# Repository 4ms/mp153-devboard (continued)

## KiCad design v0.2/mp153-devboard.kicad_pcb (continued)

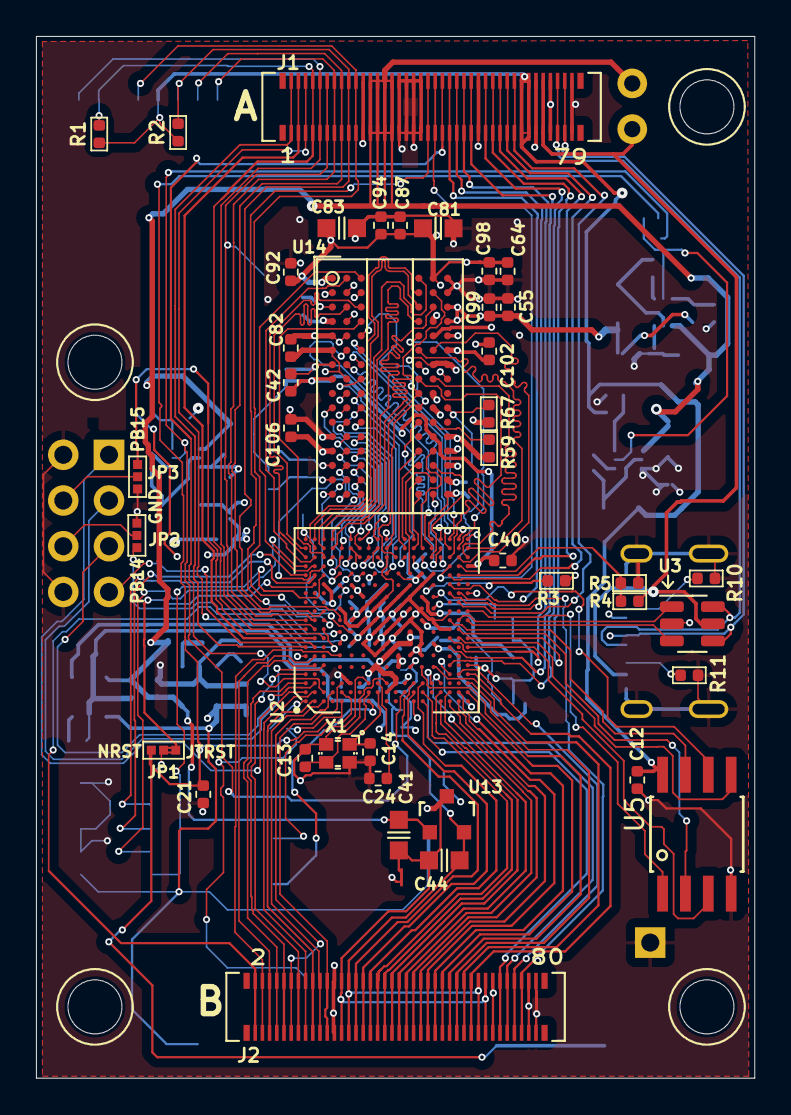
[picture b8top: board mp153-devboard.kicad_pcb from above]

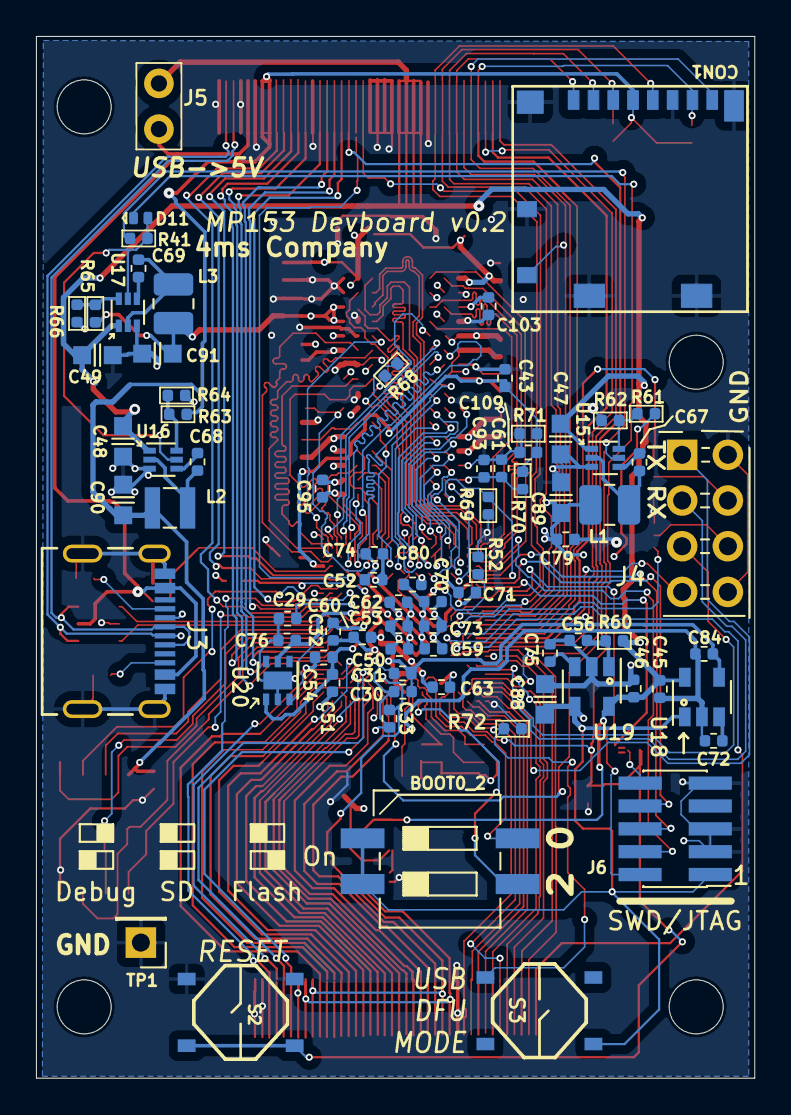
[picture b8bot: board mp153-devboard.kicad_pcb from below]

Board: 4 copper layers, 39.9 x 57.9 mm, 122 parts (76 on the bottom side), 168 nets.

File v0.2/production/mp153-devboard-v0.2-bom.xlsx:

mp153-devboard-v0.2-bom
4ms Company
PCBA Project: | mp153-devboard | Revision: | v0.2
EMAIL: | 4ms@4mscompany.com
DATE: | 2025-07-10
Group | Item# | Manufacturer | Manufacter Part# | Designator | Quantity | Designation | Package | Comments | Supplied by:
A | 1 | Hirose | DF40C-80DP-0.4V(51) | J1, J2 | 2 | Pins_02x40_P0.4mm_W3.0mm_SMT | Connector-80pin-P0.4mm-W3.0mm
A | 2 | Molex | 217179-0001 | J3 | 1 | USB-C_Receptacle_Molex_2171790001 | USB_C_Receptacle_Molex_2171790001
A | 3 | CTS | 219-2MST | BOOT0_2 | 1 | SW_DIP_x02_CTS_219-2MST, DIP Switch SPST x 2, Gull wing P2.54mm, 6.7x6.55mm Bod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 | SW_DIP_SPSTx02_CTS_219-2MSTR
A | 4 | Murata | GCM155R71C104KA55D | C12, C21, C30, C40, C42, C43, C61, C64, C67, C68, C69, C82, C87, C92, C93, C94,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 | 22 | 100nF_0402_16V, 0.1uF, Min. 16V 10%, X7R or X5R or similar | C0402
A | 5 | Yageo | CC0402CRNPO9BN6R8 | C13, C14 | 2 | 6.8pF_0402_25V, 6.8pF, Min. 25V 10%, NP0/C0G | C0402
A | 6 | Yageo | CC0402KRX7R7BB103 | C24 | 1 | 10nF_0402_16V, 10nF, Min. 16V 10%, X7R or X5R or similar | C0402
A | 7 | Murata | GRM155R60J225KE95D | C29, C32 | 2 | 2.2uF_0402_6.3V, 2.2uF, Min. 6.3V 10%, X7R or X5R or similar | C0402
A | 8 | Taiyo Yuden | GMK105CC6105KV-F | C31, C33, C45, C46, C50, C51, C52, C53, C54, C55, C59, C60, C62, C63, C70, C73,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 | 18 | 1uF_0402_25V, 1uF, Min. 25V, 0402, Ceramic/MLCC | C0402
A | 9 | Murata | GRM188R6YA225KA12D | C41, C47, C48, C49 | 4 | 2.2uF_0603_25V, 2.2uF, Min 25V 10% X5R | C0603
A | 10 | Murata | GRM188R61A106KE69D | C44, C81, C83 | 3 | 10uF_0603_10V, 10uF, Min. 10V X5R 10% | C0603
A | 11 | Murata | GRM155R71H104KE14D | C56, C72, C75 | 3 | 100nF_0402_50V, 0.1uF, Min. 50V 10%, X7R or X5R or similar | C0402
A | 12 | Vishay | VJ0402Y332KXACW1BC | C71, C74, C80 | 3 | 3.3nF_0402_16V, 3.3nF, Min. 16V 10%, X7R or X5R or similar | C0402
A | 13 | Murata | GRM155R60J475ME47 | C76, C84 | 2 | 4.7uF_0402_6.3V, 4.7uF, Min. 6.3V 20%, X7R or X5R or similar | C0402
A | 14 | Murata | GRM188R60J226MEA0J | C88, C89, C90, C91 | 4 | 22uF_0603_6.3V, 22uF, 6.3V,10%,X5R or X7R,0603 | C0603
A | 15 | Diodes Inc | BAT54LP-7 | D11 | 1 | BAT54LP, Schottky, 1mm x 0.6mm, Vr >= 30V, If >= 200mA, Vf = 240mA@0.1mA | DFN-1006-2
A | 16 | Murata | DFE252012P-1R0M=P2 | L1, L3 | 2 | 1uH_3.2A_2520, Inductor 1uH ~42mohm 3.2A 2.5mm x 2.0mm | L_1008_2520Metric
A | 17 | Bourns | SRN2510F-4R7M | L2 | 1 | 4.7uH_1.7A_2510, Power Inductors - SMD 4.7uH 20% SMD 2510 1.7A | L_Wuerth_MAPI-2510
A | 18 | Yageo | RC0402FR-0710KL | R1, R2, R41, R61, R64, R66, R67, R69, R72 | 9 | 10k_0402, 10k, 1%, 1/16W, 0402 | R0402
A | 19 | Yageo | RC0402FR-073KL | R3 | 1 | 3k_0402, 3k, 1%, 1/16W, 0402 | R0402
A | 20 | Yageo | RC0402FR-07430KL | R4 | 1 | 430k_0402, 430k, 1%, 1/16W, 0402 | R0402
A | 21 | Yageo | RC0402FR-07620KL | R5 | 1 | 620k_0402, 620k, 1%, 1/16W, 0402 | R0402
A | 22 | Yageo | RC0402FR-075K1L | R10, R11 | 2 | 5.1k_0402, 5.1k, 1%, 1/16W, 0402 | R0402
A | 23 | Yageo | RC0402FR-07240RL | R52, R59 | 2 | 240Ω_0402, 240Ω, 1%, 1/16W, 0402 | R0402
A | 24 | Yageo | RC0402FR-07100KL | R60 | 1 | 100k_0402, 100k, 1%, 1/16W, 0402 | R0402
A | 25 | Yageo | RC0402FR-0720KL | R62 | 1 | 20k_0402, 20k, 1%, 1/16W, 0402 | R0402
A | 26 | Yageo | RC0402FR-0731K6L | R63 | 1 | 31.6k_0402, 31.6k, 1%, 1/16W, 0402 | R0402
A | 27 | Yageo | RC0402FR-076K8L | R65 | 1 | 6.8k_0402, 6.8k, 1%, 1/16W, 0402 | R0402
A | 28 | Yageo | RC0402FR-07100RL | R68 | 1 | 100Ω_0402, 100Ω, 1%, 1/16W, 0402 | R0402
A | 29 | Yageo | RC0402FR-071KL | R70, R71 | 2 | 1k_0402, 1k, 1%, 1/16W, 0402 | R0402
A | 30 | C&K Switches | PTS526 SM15 SMTR2 LFS | S2, S3 | 2 | SW_Push_PTS526 SM15 SMTR2 LFS, Tact button, NO, | Button_Tact_PTS526
A | 31 | STMicroelectronics | STM32MP153DAD | U2 | 1 | STM32MP15xxAD, Cortex A7x2 + M4, 800MHz, TFBGA12x12 | TFBGA-257_10x10mm_perP0.5_cntrP0.65
A | 32 | STMicroelectronics | USBLC6-2SC6 | U3 | 1 | USBLC6-2SC6, ESD Protection, pins 3+4, 1+6 shorted | SOT-23-6
A | 33 | Winbond | W25Q128JVSIQ | U5 | 1 | NORFLASH_W25Q128JV, 16Mbit QSPI NOR FLASH, 4kb uniform sectors | SOIC-8_5.28x4.9mm_Pitch1.27mm
A | 34 | ON Semiconductor | NCP51460SN33T1G | U13 | 1 | NCP51460SN33, Precision 3.3V Ref 1% 18PPM 28Vmax 20mAmax | SOT23-3_PO132
A | 35 | Micron | MT41K256M16TW-107-P-V00H | U14 | 1 | DDR3L-RAM-4Gb_MT41K256M16TW, 4Gbit DDR3L | FBGA-96_Layout2x3x16_Body8x14_P0.8mm
A | 36 | Diodes Inc | AP62301Z6 | U15, U16, U17 | 3 | AP6230xZ6, 3A, 750kHz Buck DC/DC Converter, VinMax>=12V | SOT-563
A | 37 | Toshiba | TAR5S33TE85LF | U18, U19 | 2 | TAR5S33, LDO 3.3V, Vin >= 12V, Enable, Min Iout >= 50mA | SOT-23-5
A | 38 | Diodes Incorporated | AP2411SN-7 | U20 | 1 | AP2411SN | DFN-6-1EP_2x2mm_P0.65mm_EP1x1.6mm
A | 39 | ECS | ECS-240-8-37-CKM-TR3 | X1 | 1 | 24MHz_8pF_2x1.6mm, 24MHz 8pF Crystal Resonator, 10ppm, 2016 2x1.6mm | Crystal_2.0x1.6mm_4pin
AB | 40 | Molex | 104031-0811 | CON1 | 1 | microSDCon_SMT_104031-0811, MicroSD Card Conn Horiz SMT | CardSlot_MicroSD_Molex_104031-0811
AB | 41 | Samtec | FTSH-105-01-F-DV | J6 | 1 | Pins_02x05_P1.27mm_SMT, Header 2x5 Pins, Pitch=1.27mm, Pin Height=3mm, Vertical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 | Pins_2x05_1.27mm_SMD
B | 42 | Samtec | TSW-104-08-T-D-RA | J4 | 1 | Pins_02x04_RightAngle_P2.54mm_TH, HEADER 2x4 MALE PINS 0.100” 90deg Right Angle | Pins_2x04_P2.54mm_Horizontal_CroppedSilk
B | 43 | Samtec | TSW-102-08-T-S-RA | J5 | 1 | Conn_01x02, Pins_01x02, Header, Male Pins, 1*2, spacing 2.54mm, right angle pin | Pins_1x02_2.54mm_Horizontal_TH
 |  |  | DNP | H1, H2, H3, H4 |  | DNP | DNP
 |  |  | DNP | TP1 |  | DNP | DNP

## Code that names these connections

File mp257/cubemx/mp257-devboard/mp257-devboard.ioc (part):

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Mcu.Name=STM32MP257DAKx
Mcu.Package=VFBGA424
Mcu.UserName=STM32MP257DAKx
PA0.GPIOParameters=GPIO_Label,PinAttribute
PA0.GPIO_Label=MP257_WAKEUP
PA0.PinAttribute=Free
PA0.Signal=GPIO_Output
PA10.Signal=S_TIM2_CH2
PA12.Signal=SPI6_MOSI
PA5.GPIOParameters=PinAttribute
PA5.Mode=SAI_B_Master
PA5.PinAttribute=CortexA35SFSBLA
PA5.Signal=SAI2_SD_B
PA9.GPIOParameters=PinAttribute
PA9.Mode=SAI_B_Master
PA9.PinAttribute=CortexA35SFSBLA
PA9.Signal=SAI2_SCK_B
PB0.Signal=SPI2_SCK
PB1.GPIOParameters=PinAttribute
PB1.PinAttribute=Free
PB1.Signal=GPIO_Input
PB10.GPIOParameters=PinAttribute
PB10.Mode=Asynchronous
PB10.PinAttribute=CortexA35SFSBLA
PB10.Signal=USART1_RX
PB11.Signal=S_TIM12_CH2
PB13.GPIOParameters=PinAttribute
PB13.Mode=SAI_B_SyncSlave
PB13.PinAttribute=CortexA35SFSBLA
PB13.Signal=SAI1_SD_B
PB15.GPIOParameters=PinAttribute
PB15.Mode=IN15-Single-Ended
PB15.PinAttribute=CortexA35SFSBLA
PB15.Signal=ADC1_INP15
PB2.Signal=SPI2_MOSI
PB3.GPIOParameters=PinAttribute
PB3.PinAttribute=Free
PB3.Signal=GPIO_Input
PB4.Signal=I2C2_SDA
PB5.Signal=I2C2_SCL
PB6.Signal=UART4_RX
PB8.GPIOParameters=PinAttribute
PB8.Mode=Asynchronous
PB8.PinAttribute=CortexA35SFSBLA
PB8.Signal=USART1_TX
PC10.GPIOParameters=PinAttribute
PC10.Mode=IN5-Single-Ended
PC10.PinAttribute=CortexA35SFSBLA
PC10.Signal=ADC1_INP5
PC11.GPIOParameters=PinAttribute
PC11.Mode=IN7-Single-Ended
PC11.PinAttribute=CortexA35SFSBLA
PC11.Signal=ADC1_INP7
PC12.GPIOParameters=PinAttribute
PC12.Mode=IN17-Single-Ended
PC12.PinAttribute=CortexA35SFSBLA
PC12.Signal=ADC1_INP17
PC13.GPIOParameters=GPIO_Label,PinAttribute
PC13.GPIO_Label=PMIC_WAKEUP
PC13.PinAttribute=Free
PC13.Signal=GPIO_Output
PC3.GPIOParameters=PinAttribute
PC3.Mode=IN12-Single-Ended
PC3.PinAttribute=CortexA35SFSBLA
PC3.Signal=ADC1_INP12
PC4.Signal=SPI6_MISO
PC5.GPIOParameters=PinAttribute
PC5.Mode=IN10-Single-Ended
PC5.PinAttribute=CortexA35SFSBLA
PC5.Signal=ADC1_INP10
PC6.GPIOParameters=PinAttribute
PC6.Mode=IN9-Single-Ended
PC6.PinAttribute=CortexA35SFSBLA
PC6.Signal=ADC1_INP9
PC7.GPIOParameters=PinAttribute
PC7.Mode=IN9-Single-Ended
PC7.PinAttribute=CortexA35SFSBLA
PC7.Signal=ADC3_INP9
PC8.Signal=SPI6_NSS
PC9.GPIOParameters=PinAttribute
PC9.Mode=IN8-Single-Ended
PC9.PinAttribute=CortexA35SFSBLA
PC9.Signal=ADC1_INP8
PD0.GPIOParameters=PinAttribute
PD0.Mode=OCTOSPI1_Port1Quad
PD0.PinAttribute=BootROMA35
PD0.Signal=OCTOSPIM_P1_CLK
PD10.GPIOParameters=PinAttribute
PD10.Mode=I2C
PD10.PinAttribute=CortexA35SFSBLA
PD10.Signal=I2C4_SDA
PD11.GPIOParameters=PinAttribute
PD11.Mode=I2C
PD11.PinAttribute=CortexA35SFSBLA
PD11.Signal=I2C4_SCL
PD14.GPIOParameters=PinAttribute
PD14.Mode=I2C
PD14.PinAttribute=CortexA35SFSBLA
PD14.Signal=I2C7_SDA
PD15.GPIOParameters=PinAttribute
PD15.Mode=I2C
PD15.PinAttribute=CortexA35SFSBLA
PD15.Signal=I2C7_SCL
PD2.Signal=SPI1_NSS
PD3.GPIOParameters=PinAttribute
PD3.Mode=OCTOSPI1_Port1_NCS1
PD3.PinAttribute=BootROMA35
PD3.Signal=OCTOSPIM_P1_NCS1
PD4.GPIOParameters=PinAttribute
PD4.Mode=OCTOSPI1_Port1Quad
PD4.PinAttribute=BootROMA35
PD4.Signal=OCTOSPIM_P1_IO0
PD5.GPIOParameters=PinAttribute
PD5.Mode=OCTOSPI1_Port1Quad
PD5.PinAttribute=BootROMA35
PD5.Signal=OCTOSPIM_P1_IO1
PD6.GPIOParameters=PinAttribute
PD6.Mode=OCTOSPI1_Port1Quad
PD6.PinAttribute=BootROMA35
PD6.Signal=OCTOSPIM_P1_IO2
PD7.GPIOParameters=PinAttribute
PD7.Mode=OCTOSPI1_Port1Quad
PD7.PinAttribute=BootROMA35
PD7.Signal=OCTOSPIM_P1_IO3
PD8.GPIOParameters=GPIO_Label,PinAttribute
PD8.GPIO_Label=DEBUG1
PD8.PinAttribute=Free
PD8.Signal=GPIO_Output
PD9.GPIOParameters=GPIO_Label,PinAttribute
PD9.GPIO_Label=DEBUG0
PD9.PinAttribute=Free
PD9.Signal=GPIO_Output
PE0.GPIOParameters=PinAttribute
PE0.Mode=SD_4_bits_Wide_bus
PE0.PinAttribute=BootROMA35,CortexA35SFSBLA
PE0.Signal=SDMMC1_D2
PE1.GPIOParameters=PinAttribute
PE1.Mode=SD_4_bits_Wide_bus
PE1.PinAttribute=BootROMA35,CortexA35SFSBLA
PE1.Signal=SDMMC1_D3
PE11.GPIOParameters=PinAttribute
PE11.Mode=SAI_A_MasterWithClock
PE11.PinAttribute=CortexA35SFSBLA
PE11.Signal=SAI1_FS_A
PE12.GPIOParameters=PinAttribute
PE12.PinAttribute=Free
PE12.Signal=GPIO_Output
PE13.GPIOParameters=PinAttribute
PE13.Mode=SAI_A_MasterWithClock
PE13.PinAttribute=CortexA35SFSBLA
PE13.Signal=SAI1_SD_A
PE14.GPIOParameters=PinAttribute
PE14.Mode=SAI_A_MasterWithClock
PE14.PinAttribute=CortexA35SFSBLA
PE14.Signal=SAI1_MCLK_A
PE15.GPIOParameters=PinAttribute
PE15.Mode=SAI_A_MasterWithClock
PE15.PinAttribute=CortexA35SFSBLA
PE15.Signal=SAI1_SCK_A
PE2.GPIOParameters=PinAttribute
PE2.Mode=SD_4_bits_Wide_bus
PE2.PinAttribute=BootROMA35,CortexA35SFSBLA
PE2.Signal=SDMMC1_CMD
PE3.GPIOParameters=PinAttribute
PE3.Mode=SD_4_bits_Wide_bus
PE3.PinAttribute=BootROMA35,CortexA35SFSBLA
PE3.Signal=SDMMC1_CK
PE4.GPIOParameters=PinAttribute
PE4.Mode=SD_4_bits_Wide_bus
PE4.PinAttribute=BootROMA35,CortexA35SFSBLA
PE4.Signal=SDMMC1_D0
PE5.GPIOParameters=PinAttribute
PE5.Mode=SD_4_bits_Wide_bus
PE5.PinAttribute=BootROMA35,CortexA35SFSBLA
PE5.Signal=SDMMC1_D1
PE9.GPIOParameters=PinAttribute
PE9.PinAttribute=Free
PE9.Signal=GPIO_Input
PF0.GPIOParameters=PinAttribute
PF0.Mode=IN11-Single-Ended
PF0.PinAttribute=CortexA35SFSBLA
PF0.Signal=ADC1_INP11
PF1.GPIOParameters=PinAttribute
PF1.PinAttribute=Free
PF1.Signal=GPIO_Analog
PF10.GPIOParameters=PinAttribute
PF10.Mode=IN2-Single-Ended
PF10.PinAttribute=CortexA35SFSBLA
PF10.Signal=ADC3_INP2
PF11.GPIOParameters=PinAttribute
PF11.Mode=IN6-Single-Ended
PF11.PinAttribute=CortexA35SFSBLA
PF11.Signal=ADC3_INP6
PF12.GPIOParameters=PinAttribute
PF12.Mode=RGB888
PF12.PinAttribute=CortexA35NSSSBL,CortexA35NSOS
PF12.Signal=LTDC_CLK
PF13.GPIOParameters=PinAttribute
PF13.Mode=RGB888
PF13.PinAttribute=CortexA35NSSSBL,CortexA35NSOS
PF13.Signal=LTDC_R2
PF14.GPIOParameters=PinAttribute
PF14.Mode=RGB888
PF14.PinAttribute=CortexA35NSSSBL,CortexA35NSOS
PF14.Signal=LTDC_R3
PF15.GPIOParameters=PinAttribute
PF15.Mode=RGB888
PF15.PinAttribute=CortexA35NSSSBL,CortexA35NSOS
PF15.Signal=LTDC_R4
PF2.GPIOParameters=PinAttribute
PF2.Mode=IN13-Single-Ended
PF2.PinAttribute=CortexA35SFSBLA
PF2.Signal=ADC1_INP13
PF3.GPIOParameters=PinAttribute
PF3.Mode=IN16-Single-Ended
PF3.PinAttribute=CortexA35SFSBLA
PF3.Signal=ADC1_INP16
PF4.Signal=S_TIM4_CH4
PF5.Signal=SPI6_SCK
PF7.GPIOParameters=PinAttribute
PF7.Mode=RGB888
PF7.PinAttribute=CortexA35NSSSBL,CortexA35NSOS
PF7.Signal=LTDC_R1
PF8.GPIOParameters=PinAttribute
PF8.Mode=RGB888
PF8.PinAttribute=CortexA35NSSSBL,CortexA35NSOS
PF8.Signal=LTDC_G0
PF9.GPIOParameters=PinAttribute
PF9.Mode=SAI_A_SyncSlave
PF9.PinAttribute=CortexA35SFSBLA
PF9.Signal=SAI2_SD_A
PG1.GPIOParameters=PinAttribute
PG1.Mode=IN6-Single-Ended
PG1.PinAttribute=CortexA35SFSBLA
PG1.Signal=ADC1_INP6
PG10.GPIOParameters=PinAttribute
PG10.Mode=RGB888
PG10.PinAttribute=CortexA35NSSSBL,CortexA35NSOS
PG10.Signal=LTDC_G4
PG11.GPIOParameters=PinAttribute
PG11.Mode=RGB888
PG11.PinAttribute=CortexA35NSSSBL,CortexA35NSOS
PG11.Signal=LTDC_G5
PG12.GPIOParameters=PinAttribute
PG12.Mode=RGB888
PG12.PinAttribute=CortexA35NSSSBL,CortexA35NSOS
PG12.Signal=LTDC_G6
PG13.GPIOParameters=PinAttribute
PG13.Mode=RGB888
PG13.PinAttribute=CortexA35NSSSBL,CortexA35NSOS
PG13.Signal=LTDC_G7
PG14.GPIOParameters=PinAttribute
PG14.Mode=RGB888
PG14.PinAttribute=CortexA35NSSSBL,CortexA35NSOS
PG14.Signal=LTDC_B1
PG15.GPIOParameters=PinAttribute
PG15.Mode=RGB888
PG15.PinAttribute=CortexA35NSSSBL,CortexA35NSOS
PG15.Signal=LTDC_B2
PG2.GPIOParameters=PinAttribute
PG2.Mode=IN2-Single-Ended
PG2.PinAttribute=CortexA35SFSBLA
PG2.Signal=ADC1_INP2
PG3.GPIOParameters=PinAttribute
PG3.PinAttribute=CortexA35SFSBLA
PG3.Signal=SharedStack_PG3
PG3.Stacked=true
PG4.GPIOParameters=PinAttribute
PG4.Mode=IN4-Single-Ended
PG4.PinAttribute=CortexA35SFSBLA
PG4.Signal=ADC1_INP4
PG5.GPIOParameters=PinAttribute
PG5.Mode=RGB888
PG5.PinAttribute=CortexA35NSSSBL,CortexA35NSOS
PG5.Signal=LTDC_R5
PG6.GPIOParameters=PinAttribute
PG6.Mode=RGB888
PG6.PinAttribute=CortexA35NSSSBL,CortexA35NSOS
PG6.Signal=LTDC_R6
PG7.GPIOParameters=PinAttribute
PG7.Mode=RGB888
PG7.PinAttribute=CortexA35NSSSBL,CortexA35NSOS
PG7.Signal=LTDC_R7
PG8.GPIOParameters=PinAttribute
PG8.Mode=RGB888
PG8.PinAttribute=CortexA35NSSSBL,CortexA35NSOS
PG8.Signal=LTDC_G2
PG9.GPIOParameters=PinAttribute
PG9.Mode=RGB888
PG9.PinAttribute=CortexA35NSSSBL,CortexA35NSOS
PG9.Signal=LTDC_G3
PH10.GPIOParameters=PinAttribute
PH10.Mode=IN8-Single-Ended
PH10.PinAttribute=CortexA35SFSBLA
PH10.Signal=ADC3_INP8
PH3.GPIOParameters=GPIO_Label,PinAttribute
PH3.GPIO_Label=USB_VBUS
PH3.PinAttribute=Free
PH3.Signal=GPIO_Input
PH4.GPIOParameters=PinAttribute
PH4.Mode=RGB888
PH4.PinAttribute=CortexA35NSSSBL,CortexA35NSOS
PH4.Signal=LTDC_R0
PH5.GPIOParameters=PinAttribute
PH5.Mode=RGB888
PH5.PinAttribute=CortexA35NSSSBL,CortexA35NSOS
PH5.Signal=LTDC_G1
PH7.Signal=S_TIM17_CH1
PH8.Signal=S_TIM5_CH1
PH9.GPIOParameters=PinAttribute
PH9.Mode=IN4-Single-Ended
PH9.PinAttribute=CortexA35SFSBLA
PH9.Signal=ADC3_INP4
PI0.GPIOParameters=PinAttribute
PI0.Mode=RGB888
PI0.PinAttribute=CortexA35NSSSBL,CortexA35NSOS
PI0.Signal=LTDC_B3
PI1.GPIOParameters=PinAttribute
PI1.Mode=RGB888

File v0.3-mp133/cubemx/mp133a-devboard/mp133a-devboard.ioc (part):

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Mcu.Name=STM32MP133AAFx
Mcu.Package=TFBGA320
Mcu.UserName=STM32MP133AAFx
PA0.GPIOParameters=PinAttribute
PA0.Mode=IN7-Single-Ended
PA0.PinAttribute=Application
PA0.Signal=ADC1_INP7
PA1.GPIOParameters=PinAttribute
PA1.Mode=IN3-Single-Ended
PA1.PinAttribute=Application
PA1.Signal=ADC1_INP3
PA10.GPIOParameters=PinAttribute
PA10.PinAttribute=Application
PA10.Signal=S_TIM1_CH3
PA11.GPIOParameters=PinAttribute
PA11.Mode=I2C
PA11.PinAttribute=Application
PA11.Signal=I2C5_SCL
PA2.GPIOParameters=PinAttribute
PA2.Mode=IN1-Single-Ended
PA2.PinAttribute=Application
PA2.Signal=ADC1_INP1
PA3.GPIOParameters=PinAttribute
PA3.Mode=IN12-Single-Ended
PA3.PinAttribute=Application
PA3.Signal=ADC1_INP12
PA4.GPIOParameters=PinAttribute
PA4.Mode=IN14-Single-Ended
PA4.PinAttribute=Application
PA4.Signal=ADC1_INP14
PA5.GPIOParameters=PinAttribute
PA5.Mode=IN2-Single-Ended
PA5.PinAttribute=Application
PA5.Signal=ADC1_INP2
PA6.GPIOParameters=PinAttribute
PA6.Mode=IN17-Single-Ended
PA6.PinAttribute=Application
PA6.Signal=ADC1_INP17
PA7.GPIOParameters=PinAttribute
PA7.Mode=IN16-Single-Ended
PA7.PinAttribute=Application
PA7.Signal=ADC1_INP16
PA9.GPIOParameters=PinAttribute
PA9.PinAttribute=Application
PA9.Signal=S_TIM1_CH2
PB1.GPIOParameters=PinAttribute
PB1.Mode=IN5-Single-Ended
PB1.PinAttribute=Application
PB1.Signal=ADC1_INP5
PB14.GPIOParameters=PinAttribute
PB14.PinAttribute=Free
PB14.Signal=GPIO_Output
PB15.GPIOParameters=PinAttribute
PB15.PinAttribute=Application
PB15.Signal=SPI4_MOSI
PB2.GPIOParameters=PinAttribute
PB2.Mode=Single Bank 1
PB2.PinAttribute=Application
PB2.Signal=QUADSPI_BK1_NCS
PB3.GPIOParameters=GPIO_Label,PinAttribute
PB3.GPIO_Label=CONSOLE_UART_RX
PB3.Mode=Asynchronous
PB3.PinAttribute=Application
PB3.Signal=UART7_RX
PB4.GPIOParameters=PinAttribute
PB4.PinAttribute=Application
PB4.Signal=S_TIM3_CH1
PB5.GPIOParameters=PinAttribute
PB5.PinAttribute=Application
PB5.Signal=S_TIM3_CH2
PB6.Signal=S_TIM4_CH1
PB8.Signal=S_TIM4_CH3
PB9.GPIOParameters=PinAttribute
PB9.PinAttribute=Free
PB9.Signal=GPIO_Input
PC1.GPIOParameters=PinAttribute
PC1.Mode=IN2-Single-Ended
PC1.PinAttribute=Application
PC1.Signal=ADC2_INP2
PC10.GPIOParameters=PinAttribute
PC10.Mode=SD_4_bits_Wide_bus
PC10.PinAttribute=Application
PC10.Signal=SDMMC1_D2
PC11.GPIOParameters=PinAttribute
PC11.Mode=SD_4_bits_Wide_bus
PC11.PinAttribute=Application
PC11.Signal=SDMMC1_D3
PC12.GPIOParameters=PinAttribute
PC12.Mode=SD_4_bits_Wide_bus
PC12.PinAttribute=Application
PC12.Signal=SDMMC1_CK
PC2.GPIOParameters=PinAttribute
PC2.Mode=IN15-Single-Ended
PC2.PinAttribute=Application
PC2.Signal=ADC1_INP15
PC3.GPIOParameters=PinAttribute
PC3.Mode=IN13-Single-Ended
PC3.PinAttribute=Application
PC3.Signal=ADC1_INP13
PC4.GPIOParameters=PinAttribute
PC4.Mode=IN4-Single-Ended
PC4.PinAttribute=Application
PC4.Signal=ADC1_INP4
PC5.GPIOParameters=PinAttribute
PC5.Mode=IN10-Single-Ended
PC5.PinAttribute=Application
PC5.Signal=ADC1_INP10
PC7.GPIOParameters=PinAttribute
PC7.PinAttribute=Application
PC7.Signal=S_TIM8_CH2
PC8.GPIOParameters=PinAttribute
PC8.Mode=SD_4_bits_Wide_bus
PC8.PinAttribute=Application
PC8.Signal=SDMMC1_D0
PC9.GPIOParameters=PinAttribute
PC9.Mode=SD_4_bits_Wide_bus
PC9.PinAttribute=Application
PC9.Signal=SDMMC1_D1
PD0.GPIOParameters=PinAttribute
PD0.Mode=SAI_A_MasterWithClock
PD0.PinAttribute=Application
PD0.Signal=SAI1_MCLK_A
PD12.GPIOParameters=PinAttribute
PD12.Mode=I2C
PD12.PinAttribute=Application
PD12.Signal=I2C1_SCL
PD14.GPIOParameters=PinAttribute
PD14.Mode=I2C
PD14.PinAttribute=Application
PD14.Signal=I2C3_SDA
PD2.GPIOParameters=PinAttribute
PD2.Mode=SD_4_bits_Wide_bus
PD2.PinAttribute=Application
PD2.Signal=SDMMC1_CMD
PD3.Signal=S_TIM2_CH1_ETR
PD6.GPIOParameters=PinAttribute
PD6.Mode=SAI_A_MasterWithClock
PD6.PinAttribute=Application
PD6.Signal=SAI1_SD_A
PD7.GPIOParameters=PinAttribute
PD7.PinAttribute=Free
PD7.Signal=GPIO_Input
PE11.GPIOParameters=PinAttribute
PE11.Mode=SAI_A_MasterWithClock
PE11.PinAttribute=Application
PE11.Signal=SAI1_FS_A
PE12.GPIOParameters=PinAttribute
PE12.Mode=Forced Output3 CH3N
PE12.PinAttribute=Application
PE12.Signal=TIM1_CH3N
PE13.GPIOParameters=PinAttribute
PE13.Mode=I2C
PE13.PinAttribute=Application
PE13.Signal=I2C5_SDA
PE5.GPIOParameters=PinAttribute
PE5.PinAttribute=Application
PE5.Signal=S_TIM15_CH1
PE8.GPIOParameters=PinAttribute
PE8.Mode=I2C
PE8.PinAttribute=Application
PE8.Signal=I2C1_SDA
PF0.GPIOParameters=GPIO_Label,PinAttribute
PF0.GPIO_Label=DEBUG3
PF0.PinAttribute=Free
PF0.Signal=GPIO_Output
PF1.GPIOParameters=PinAttribute
PF1.Mode=Full_Duplex_Master
PF1.PinAttribute=Application
PF1.Signal=SPI3_MOSI
PF10.GPIOParameters=PinAttribute
PF10.Mode=Single Bank 1
PF10.PinAttribute=Application
PF10.Signal=QUADSPI_CLK
PF11.GPIOParameters=PinAttribute
PF11.Mode=IN8-Single-Ended
PF11.PinAttribute=Application
PF11.Signal=ADC1_INP8
PF12.GPIOParameters=PinAttribute
PF12.Mode=IN6-Single-Ended
PF12.PinAttribute=Application
PF12.Signal=ADC1_INP6
PF14.GPIOParameters=PinAttribute
PF14.Mode=JTAG_5_pins
PF14.PinAttribute=Application
PF14.Signal=DEBUG_JTCK-SWCLK
PF15.GPIOParameters=PinAttribute
PF15.Mode=JTAG_5_pins
PF15.PinAttribute=Application
PF15.Signal=DEBUG_JTMS-SWDIO
PF3.GPIOParameters=PinAttribute
PF3.Mode=NSS_Signal_Hard_Output
PF3.PinAttribute=Application
PF3.Signal=SPI3_NSS
PF6.GPIOParameters=PinAttribute
PF6.Mode=Single Bank 1
PF6.PinAttribute=Application
PF6.Signal=QUADSPI_BK1_IO2
PF8.GPIOParameters=PinAttribute
PF8.Mode=Single Bank 1
PF8.PinAttribute=Application
PF8.Signal=QUADSPI_BK1_IO0
PF9.GPIOParameters=PinAttribute
PF9.Mode=Single Bank 1
PF9.PinAttribute=Application
PF9.Signal=QUADSPI_BK1_IO1
PG0.GPIOParameters=PinAttribute
PG0.PinAttribute=Free
PG0.Signal=GPIO_Input
PG10.GPIOParameters=PinAttribute
PG10.Mode=SAI_B_SyncSlave
PG10.PinAttribute=Application
PG10.Signal=SAI1_SD_B
PG12.GPIOParameters=PinAttribute
PG12.PinAttribute=Application
PG12.Signal=SAI2_SCK_A
PG13.GPIOParameters=PinAttribute
PG13.Mode=IN6-Single-Ended
PG13.PinAttribute=Application
PG13.Signal=ADC2_INP6
PG2.GPIOParameters=PinAttribute
PG2.PinAttribute=Free
PG2.Signal=GPIO_Input
PG4.GPIOParameters=GPIO_Label,PinAttribute
PG4.GPIO_Label=DEBUG2
PG4.PinAttribute=Free
PG4.Signal=GPIO_Output
PG7.GPIOParameters=PinAttribute
PG7.Mode=Full_Duplex_Master
PG7.PinAttribute=Application
PG7.Signal=SPI3_MISO
PH0-OSC_IN.GPIOParameters=PinAttribute
PH0-OSC_IN.Mode=HSE-External-Oscillator
PH0-OSC_IN.PinAttribute=FirstStageBootLoader,Application
PH0-OSC_IN.Signal=RCC_OSC_IN
PH1-OSC_OUT.GPIOParameters=PinAttribute
PH1-OSC_OUT.Mode=HSE-External-Oscillator
PH1-OSC_OUT.PinAttribute=FirstStageBootLoader,Application
PH1-OSC_OUT.Signal=RCC_OSC_OUT
PH12.GPIOParameters=PinAttribute
PH12.Mode=SAI_A_MasterWithClock
PH12.PinAttribute=Application
PH12.Signal=SAI1_SCK_A
PH13.GPIOParameters=PinAttribute
PH13.Mode=Full_Duplex_Master
PH13.PinAttribute=Application
PH13.Signal=SPI3_SCK
PH14.GPIOParameters=PinAttribute
PH14.PinAttribute=Free
PH14.Signal=GPIO_Input
PH2.GPIOParameters=GPIO_Label,PinAttribute
PH2.GPIO_Label=CONSOLE_UART_TX
PH2.Mode=Asynchronous
PH2.PinAttribute=Application
PH2.Signal=UART7_TX
PH3.GPIOParameters=PinAttribute
PH3.Mode=I2C
PH3.PinAttribute=Application
PH3.Signal=I2C3_SCL
PH4.GPIOParameters=PinAttribute
PH4.Mode=JTAG_5_pins
PH4.PinAttribute=Application
PH4.Signal=DEBUG_JTDI
PH5.GPIOParameters=PinAttribute
PH5.Mode=JTAG_5_pins
PH5.PinAttribute=Application
PH5.Signal=DEBUG_JTDO-SWO
PH7.GPIOParameters=PinAttribute
PH7.Mode=Single Bank 1
PH7.PinAttribute=Application
PH7.Signal=QUADSPI_BK1_IO3
PH8.Signal=USART2_RX
PI4-BOOT0.GPIOParameters=PinAttribute
PI4-BOOT0.PinAttribute=Free
PI4-BOOT0.Signal=GPIO_Input
PI6-BOOT2.GPIOParameters=PinAttribute
PI6-BOOT2.PinAttribute=Free
PI6-BOOT2.Signal=GPIO_Input
PI7.GPIOParameters=PinAttribute
PI7.Mode=Activate_VBUS_FS
PI7.PinAttribute=Application
PI7.Signal=USB_OTG_HS_VBUS
RCC.HSE_VALUE=24000000
RCC.SYSCLKFreq_VALUE=208895996.09375
board=custom

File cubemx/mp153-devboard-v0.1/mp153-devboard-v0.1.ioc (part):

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Mcu.Name=STM32MP153DADx
Mcu.Package=TFBGA257
Mcu.UserName=STM32MP153DADx
PA0.Mode=IN16-Single-Ended
PA0.Signal=ADC1_INP16
PA1.Mode=IN17-Single-Ended
PA1.Signal=ADC1_INP17
PA10.Signal=GPIO_Input
PA11.Mode=I2C
PA11.Signal=I2C5_SCL
PA12.Mode=I2C
PA12.Signal=I2C5_SDA
PA15.GPIOParameters=GPIO_Label
PA15.GPIO_Label=DEBUG3
PA15.Signal=GPIO_Output
PA2.Signal=ADCx_INP14
PA3.Signal=ADCx_INP15
PA4.Signal=ADCx_INP18
PA5.Signal=ADCx_INP19
PA6.Signal=ADCx_INP3
PA7.Signal=ADCx_INP7
PA8.Signal=GPIO_Input
PA9.Signal=GPIO_Input
PB0.Signal=ADCx_INP9
PB1.Signal=ADCx_INP5
PB14.Mode=Full_Duplex_Master
PB14.Signal=SPI2_MISO
PB15.Mode=Full_Duplex_Master
PB15.Signal=SPI2_MOSI
PB2.Mode=SAI_A_MasterWithClock
PB2.Signal=SAI1_SD_A
PB4.Signal=GPIO_Output
PB6.Mode=Single Bank 1
PB6.Signal=QUADSPI_BK1_NCS
PB7.Mode=I2C
PB7.Signal=I2C1_SDA
PB8.Mode=I2C
PB8.Signal=I2C1_SCL
PB9.GPIOParameters=GPIO_Label
PB9.GPIO_Label=DEBUG2
PB9.Signal=GPIO_Output
PC0.Signal=ADCx_INP10
PC1.Signal=ADCx_INP11
PC10.Mode=SD_4_bits_Wide_bus
PC10.Signal=SDMMC1_D2
PC11.Mode=SD_4_bits_Wide_bus
PC11.Signal=SDMMC1_D3
PC12.Mode=SD_4_bits_Wide_bus
PC12.Signal=SDMMC1_CK
PC2.Signal=ADCx_INP12
PC3.Signal=ADCx_INP13
PC4.Signal=ADCx_INP4
PC5.Signal=ADCx_INP8
PC6.Mode=Asynchronous
PC6.Signal=USART6_TX
PC7.Mode=Asynchronous
PC7.Signal=USART6_RX
PC8.Mode=SD_4_bits_Wide_bus
PC8.Signal=SDMMC1_D0
PC9.Mode=SD_4_bits_Wide_bus
PC9.Signal=SDMMC1_D1
PD0.Mode=I2C
PD0.Signal=I2C6_SDA
PD1.Mode=I2C
PD1.Signal=I2C6_SCL
PD11.Mode=SAI_A_MasterWithClock
PD11.Signal=SAI2_SD_A
PD12.Mode=SAI_A_MasterWithClock
PD12.Signal=SAI2_FS_A
PD13.Mode=SAI_A_MasterWithClock
PD13.Signal=SAI2_SCK_A
PD2.Mode=SD_4_bits_Wide_bus
PD2.Signal=SDMMC1_CMD
PD3.Mode=Full_Duplex_Master
PD3.Signal=SPI2_SCK
PD7.Signal=GPIO_Output
PD8.GPIOParameters=GPIO_Label
PD8.GPIO_Label=DFU_BOOT
PD8.Signal=GPIO_Input
PE0.Mode=SAI_A_MasterWithClock
PE0.Signal=SAI2_MCLK_A
PE10.Signal=GPIO_Output
PE11.GPIOParameters=GPIO_Label
PE11.GPIO_Label=DEBUG3
PE11.Signal=GPIO_Output
PE12.Mode=Full_Duplex_Master
PE12.Signal=SPI4_SCK
PE13.Mode=Full_Duplex_Master
PE13.Signal=SPI4_MISO
PE2.Mode=SAI_A_MasterWithClock
PE2.Signal=SAI1_MCLK_A
PE3.Mode=SAI_B_SyncSlave
PE3.Signal=SAI1_SD_B
PE4.GPIOParameters=GPIO_Label
PE4.GPIO_Label=SD_DETECT
PE4.Signal=GPIO_Input
PE6.Mode=Full_Duplex_Master
PE6.Signal=SPI4_MOSI
PF10.Mode=Single Bank 1
PF10.Signal=QUADSPI_CLK
PF11.Mode=IN2-Single-Ended
PF11.Signal=ADC1_INP2
PF6.Mode=Single Bank 1
PF6.Signal=QUADSPI_BK1_IO3
PF7.Mode=Single Bank 1
PF7.Signal=QUADSPI_BK1_IO2
PF8.Mode=Single Bank 1
PF8.Signal=QUADSPI_BK1_IO0
PF9.Mode=Single Bank 1
PF9.Signal=QUADSPI_BK1_IO1
PG10.Mode=SAI_B_SyncSlave
PG10.Signal=SAI2_SD_B
PG13.Mode=SAI_A_MasterWithClock
PG13.Signal=SAI1_SCK_A
PG15.Mode=SAI_A_MasterWithClock
PG15.Signal=SAI1_FS_A
PG9.Signal=GPIO_Output
PH0-OSC_IN.Mode=HSE-External-Clock-Source
PH0-OSC_IN.Signal=RCC_OSC_IN
PH1-OSC_OUT.Mode=HSE-External-Clock-Source
PH1-OSC_OUT.Signal=RCC_OSC_OUT
RCC.HSE_VALUE=24000000
board=custom

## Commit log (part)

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2025-06-03 Start v0.1 devboard
2025-06-03 WIP routing v0.1
2025-06-03 Rename project files
2025-06-03 Finish v0.1 dev board
2025-06-03 Generate JLC and generic/Posin production files
2025-06-03 Move project to v0.1 folder
2025-06-04 v0.1: add microSD slot, use USB-C, jumper for USB power, boot switches
2025-06-04 Start carrier board
2025-06-04 Update BOM with JLC numbers
2025-06-04 Ignore backup files
2025-06-04 Add JLC numbers
2025-06-04 Cleanup carrier board example
2025-06-11 Carrier-board: Added codec and audio in/out
2025-06-11 Finished carrier board. Produced JLC files
2025-06-11 JLC files for carrier board. Ordered
2025-06-11 devboard v0.1: increased spacing between zones on inner layers. Vias => 0.25mm holes
2025-06-11 Fix silk overlap on 80pin connector footprint
2025-06-11 Exported production files for v0.1 devboard
2025-06-11 Update devboard v0.1 with 0.3mm minimum via hole. Ordered JLCPCB
2025-06-23 Start p2 carrier board
2025-06-24 p2 carrier board: fixed position of headers
2025-06-24 Move carrier board to v0.1 dir. Rename p2=>v0.2
2025-06-24 Add note to devboard schematic
2025-06-26 Schematic notes (v0.1)
2025-06-26 More notes on v0.1 devboard schematic. Updated cubemx file for v0.1
2025-06-30 Add 3d model of devboard
2025-07-02 Add symbols for devboard
2025-07-02 Symbol tables use new mp153 sym lib
2025-07-02 devboard v0.1: rename all header pins
    No electrical changes made: only renamed pins to use PX# style (e.g. "PA0") instead of D# style (e.g. "D23")
2025-07-02 devboard symbol: pin A39 should be unconnected
    For future revisions, it will be a pin, so carrier boards shouldn't ground it
2025-07-02 Add footprint for mp153 devboard
2025-07-02 Cubemx: export pinout.csv
2025-07-02 Create carrier board v0.3:
    - Fix D+/D- swap on USB jack
    - Generate +5V from +12V
    - Use symbol and footprint
2025-07-02 symbol: add title
2025-07-02 carrier board v0.3: finish schematic and PCB
2025-07-02 carrier board: fix-it notes for v0.2
2025-07-03 JLC Producton files for carrier board v0.3
2025-07-05 symbols: create guide A and guide B symbols
2025-07-05 Create A and B socket footprints
2025-07-05 Start v0.4 (to test out new footprints/sym)
    Compared gerbers vs v0.3:
    - Mask opening along center of 2x40 connectors (was traces, now is one extended pad)
    - B68 via now connects to GND (may have been an error on v0.3?)
    - Minor silk changes (around jacks and 2x40s).
2025-07-11 Create and order v0.2 devboard (Posin)
    Moved v0.1 board to v0.1 dir
2025-07-11 Hide 1x1 GND header 3d model
2025-07-17 v0.2: Update AP62301Z6 part numbers
2025-07-30 update mp153-devboard symbol pins
2025-07-30 rgb carrier board v0.1
2025-09-09 v0.3 and v0.4 carrier board
2025-09-09 v0.1 symbol: Add part numbers for Hirose connectors
2025-09-09 Footprint: Remove version text
2025-09-09 Add v0.2 devboard symbol
2025-12-11 Add v0.3-mp135 project
2025-12-11 Rename mp135 board to v0.3-mp133
2025-12-11 mp133 schematic WIP
2025-12-11 v0.2 uart connection image
2025-12-11 TODO note for v0.2 board
2025-12-11 carrier-board v0.4: notes and updates
2025-12-12 mp133 devboard sch WIP
2025-12-13 Work on mp133 devboard PCB
2025-12-16 mp133 devboard DDR routing started
2025-12-17 mp133: add DDR pins escaped or has via
2025-12-17 mp13x: DDR3 RAM routed
2025-12-22 WIP Routing
2025-12-24 Created breakoutboard project
2025-12-27 Laying out board - WIP
2025-12-28 Organized breakoutheader silk
2025-12-29 WIP - completeing traces
2025-12-29 Begin fixing audio out section
2025-12-29 Resolved ERC and DRC errors - warnings need to be reviewed. Cleaned up silk and cleaned up Audio out opamp section
2025-12-29 Removed redundant ADC net labels
2025-12-29 Project files updated to kicad 9.0.6
2025-12-29 carrier-breakout cleanup:
    - Fix nets with two names
    - Fix some silk overlap DRC warning for components too close
    - Add more space for pins names to fix DRC warnings for silk sizes
    - Remove empty boxes on silk
    - Space out jumpers that we may have to cut with an exacto (more space = easier to cut)
    - Added jumper for USB_5V_ENABLE, and pull-down to prevent floating when jumper is cut
2025-12-29 carrier-breakout: Production files (ordered JLC PCBA)
2025-12-29 mp133: WIP routing and pin assignment
2025-12-30 mp133 cubemx: pin assignment
2025-12-30 mp133: routing and pin assignment
2025-12-30 mp133: completed routing
2025-12-30 mp133: cleanup for production
2025-12-30 mp133: Ordered JLC PCBA. Production files
2026-01-02 PCB for mp133 v0.4 (length-matched some DDR_Q traces)
2026-01-13 mp133: Update cubemx
2026-02-15 Start mp25x project
2026-02-15 mp25x reference projects
2026-02-16 mp25x v0.1 WIP
2026-02-17 Copy v0.3-mp133 schematic and tables to v0.4-mp133
2026-02-18 mp25x v0.1: removed mp135 and associated
2026-02-18 Ignore backups
2026-02-20 Add sdprog project
2026-02-20 Cleanup sdprog
2026-02-20 JLC production files for sdprog
2026-02-20 Fix ref nums pasted from reference schematic
2026-02-20 Fix all refs: no duplicates
2026-02-20 pcb: removed extra stuff on devboard
2026-02-21 WIP: symbols
2026-02-21 Updated RAM and STM32MP2 footprints to 4ms lib
2026-02-22 Updating parts to 4ms lib
2026-02-23 Ignore .history files
2026-02-23 Update remaining parts to 4ms lib
2026-02-25 Caps
2026-02-25 Fix caps
2026-02-27 pmic placement
2026-02-28 mp257 cubemx
2026-02-28 mp257 placement WIP
2026-03-02 cubemx generated DDR reg values
2026-03-03 cubemx project updated
2026-03-03 Mark: before re-doing RAM
2026-03-03 DQ ram traces length matched
2026-03-03 Original trace lengths
2026-03-03 Traces spreadsheets
2026-03-03 All DDR nets length matched, and exported net report
2026-03-06 Routing SDMMC, SAI, I2C, ADCs
2026-03-07 Header B almost fully routed
2026-03-09 Routing...
2026-03-09 Routing
2026-03-10 Routing: moved chips closer to B header
2026-03-13 Routing WIP
2026-03-19 WIP routing pmic
2026-03-27 Silk cleanup, final routing
2026-03-28 mp257 devboard: pass DRC + ERC
2026-04-02 cubemx updated with pinout
2026-04-02 Cleanup BOM, update all parts from lib
2026-04-02 Export production files (WIP)
2026-04-02 Fixing missing M P/N
2026-04-02 Missing p/n
2026-04-06 Finish board, cleanup BOM
2026-04-06 Production files for proto run to Posin
2026-06-19 BOOT pin notes
2026-06-30 Export cubemx for mp257
2026-06-30 Change cubemx: DDR ram at 640MHz
2026-06-30 Add BOM EQ for mp257 v0.1
